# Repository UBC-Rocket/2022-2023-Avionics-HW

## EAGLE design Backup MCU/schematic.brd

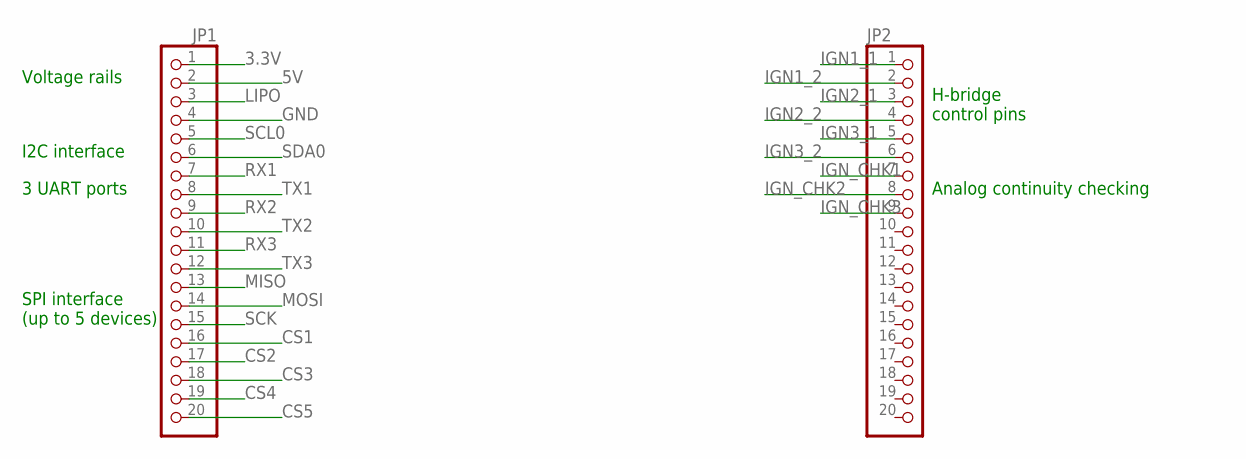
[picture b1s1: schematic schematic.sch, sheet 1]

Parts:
JP1, JP2: PINHD-1X20; 1X20

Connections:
3.3V: JP1.1; also elsewhere on the board
5V: JP1.2
CS1: JP1.16
CS2: JP1.17
CS3: JP1.18
CS4: JP1.19
CS5: JP1.20
GND: JP1.4; also elsewhere on the board
IGN1_1: JP2.1; also elsewhere on the board
IGN1_2: JP2.2; also elsewhere on the board
IGN2_1: JP2.3; also elsewhere on the board
IGN2_2: JP2.4; also elsewhere on the board
IGN3_1: JP2.5; also elsewhere on the board
IGN3_2: JP2.6; also elsewhere on the board
IGN_CHK1: JP2.7; also elsewhere on the board
IGN_CHK2: JP2.8; also elsewhere on the board
IGN_CHK3: JP2.9; also elsewhere on the board
LIPO: JP1.3; also elsewhere on the board
MISO: JP1.13
MOSI: JP1.14
RX1: JP1.7; also elsewhere on the board
RX2: JP1.9; also elsewhere on the board
RX3: JP1.11
SCK: JP1.15
SCL0: JP1.5; also elsewhere on the board
SDA0: JP1.6; also elsewhere on the board
TX1: JP1.8; also elsewhere on the board
TX2: JP1.10; also elsewhere on the board
TX3: JP1.12

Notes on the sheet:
SPI interface (up to 5 devices)
3 UART ports
I2C interface
Voltage rails
H-bridge control pins
Analog continuity checking

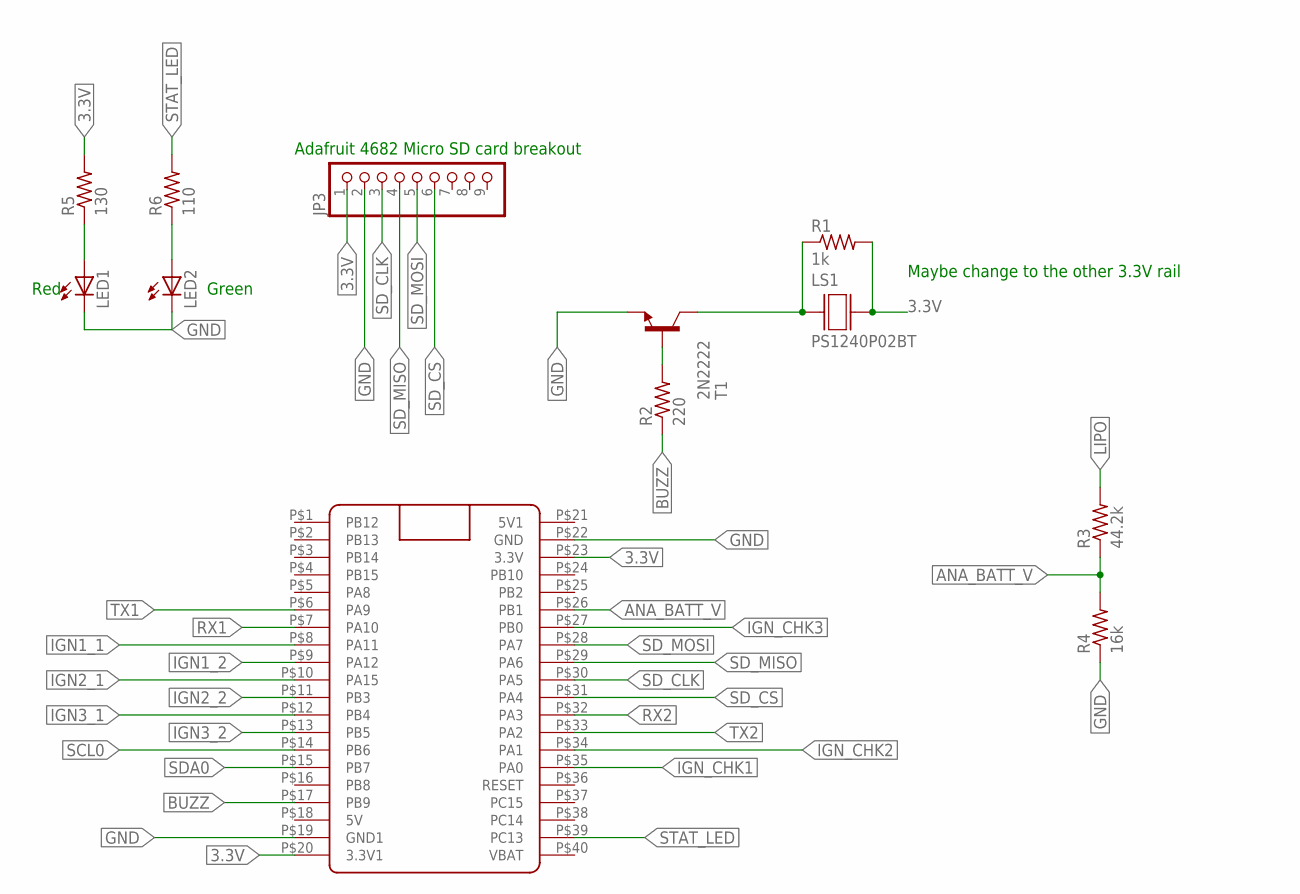
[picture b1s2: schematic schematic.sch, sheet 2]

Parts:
JP3: PINHD-1X9; 1X09-BIG
LED1, LED2: LED5MM
LS1: PS1240P02BT; XDCR_PS1240P02BT
R1: 1k; 0204/7
R2: 220; 0204/7
R3: 44.2k; 0204/7
R4: 16k; 0204/7
R5: 130; 0204/7
R6: 110; 0204/7
T1: 2N2222; TO92-EBC-OVAL
U$1: BLACK_PILL

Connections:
3.3V: JP3.1, LS1.2, R1.2, R5.2, U$1.P$20 (3.3V1), U$1.P$23 (3.3V); also elsewhere on the board
ANA_BATT_V: R3.1, R4.2, U$1.P$26 (PB1)
BUZZ: R2.1, U$1.P$17 (PB9)
GND: JP3.2, LED1.K (C), LED2.K (C), R4.1, T1.E, U$1.P$19 (GND1), U$1.P$22 (GND); also elsewhere on the board
IGN1_1: U$1.P$8 (PA11); also elsewhere on the board
IGN1_2: U$1.P$9 (PA12); also elsewhere on the board
IGN2_1: U$1.P$10 (PA15); also elsewhere on the board
IGN2_2: U$1.P$11 (PB3); also elsewhere on the board
IGN3_1: U$1.P$12 (PB4); also elsewhere on the board
IGN3_2: U$1.P$13 (PB5); also elsewhere on the board
IGN_CHK1: U$1.P$35 (PA0); also elsewhere on the board
IGN_CHK2: U$1.P$34 (PA1); also elsewhere on the board
IGN_CHK3: U$1.P$27 (PB0); also elsewhere on the board
LIPO: R3.2; also elsewhere on the board
unnamed: LS1.1, R1.1, T1.C
unnamed: LED1.A, R5.1
unnamed: R2.2, T1.B
unnamed: LED2.A, R6.1
RX1: U$1.P$7 (PA10); also elsewhere on the board
RX2: U$1.P$32 (PA3); also elsewhere on the board
SCL0: U$1.P$14 (PB6); also elsewhere on the board
SDA0: U$1.P$15 (PB7); also elsewhere on the board
SD_CLK: JP3.3, U$1.P$30 (PA5)
SD_CS: JP3.6, U$1.P$31 (PA4)
SD_MISO: JP3.4, U$1.P$29 (PA6)
SD_MOSI: JP3.5, U$1.P$28 (PA7)
STAT_LED: R6.2, U$1.P$39 (PC13)
TX1: U$1.P$6 (PA9); also elsewhere on the board
TX2: U$1.P$33 (PA2); also elsewhere on the board

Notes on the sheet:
Adafruit 4682 Micro SD card breakout
Maybe change to the other 3.3V rail
Green
Red

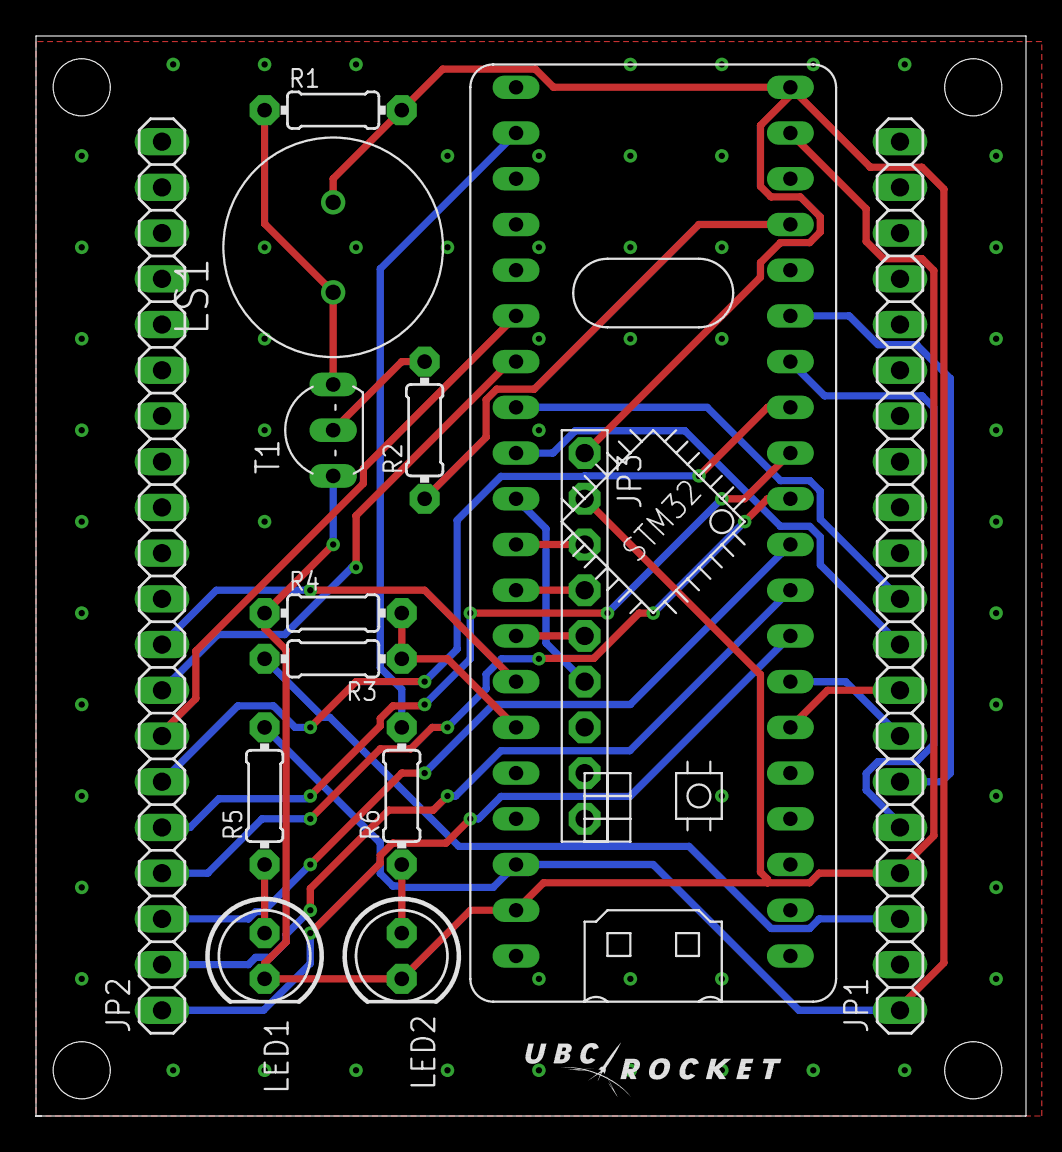
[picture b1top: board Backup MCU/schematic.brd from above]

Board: 2 copper layers, 55.0 x 60.0 mm, 14 parts (0 on the bottom side), 29 nets.

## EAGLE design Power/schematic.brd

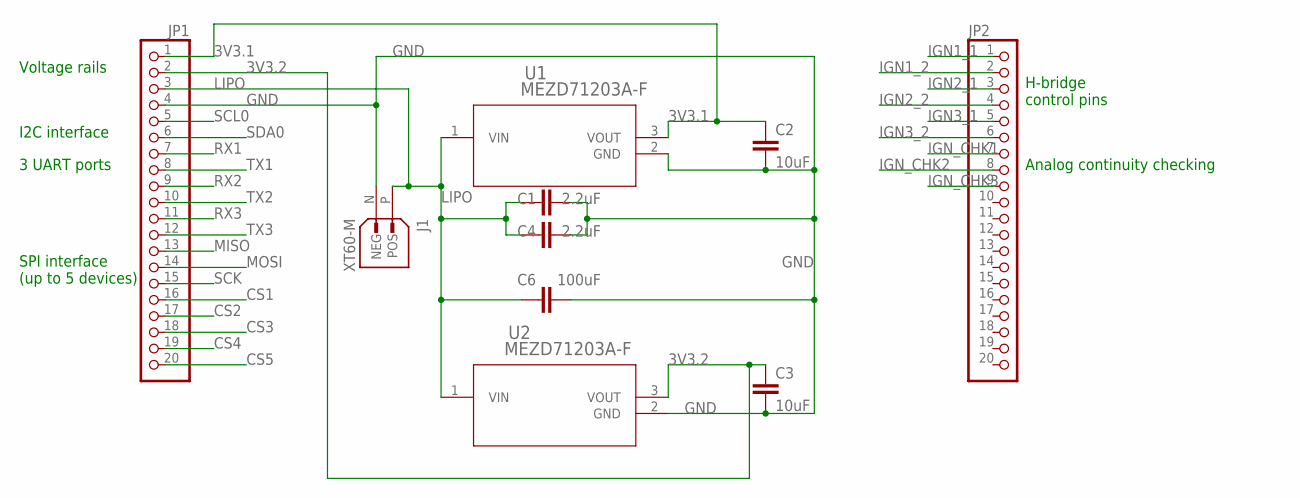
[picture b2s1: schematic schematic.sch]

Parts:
C1, C4: 2.2uF; C0805
C2, C3: 10uF; C0805
C6: 100uF; C0805
J1: XT60-M; AMASS_XT60-M
JP1, JP2: PINHD-1X20; 1X20
U1, U2: MEZD71203A-F; MEZD71203A_MNP

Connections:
3V3.1: C2.1, JP1.1, U1.3 (VOUT)
3V3.2: C3.1, JP1.2, U2.3 (VOUT)
CS1: JP1.16
CS2: JP1.17
CS3: JP1.18
CS4: JP1.19
CS5: JP1.20
GND: C1.2, C2.2, C3.2, C4.2, C6.2, J1.N (NEG), JP1.4, U1.2 (GND), U2.2 (GND)
IGN1_1: JP2.1
IGN1_2: JP2.2
IGN2_1: JP2.3
IGN2_2: JP2.4
IGN3_1: JP2.5
IGN3_2: JP2.6
IGN_CHK1: JP2.7
IGN_CHK2: JP2.8
IGN_CHK3: JP2.9
LIPO: C1.1, C4.1, C6.1, J1.P (POS), JP1.3, U1.1 (VIN), U2.1 (VIN)
MISO: JP1.13
MOSI: JP1.14
RX1: JP1.7
RX2: JP1.9
RX3: JP1.11
SCK: JP1.15
SCL0: JP1.5
SDA0: JP1.6
TX1: JP1.8
TX2: JP1.10
TX3: JP1.12

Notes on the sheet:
SPI interface (up to 5 devices)
3 UART ports
I2C interface
Voltage rails
H-bridge control pins
Analog continuity checking

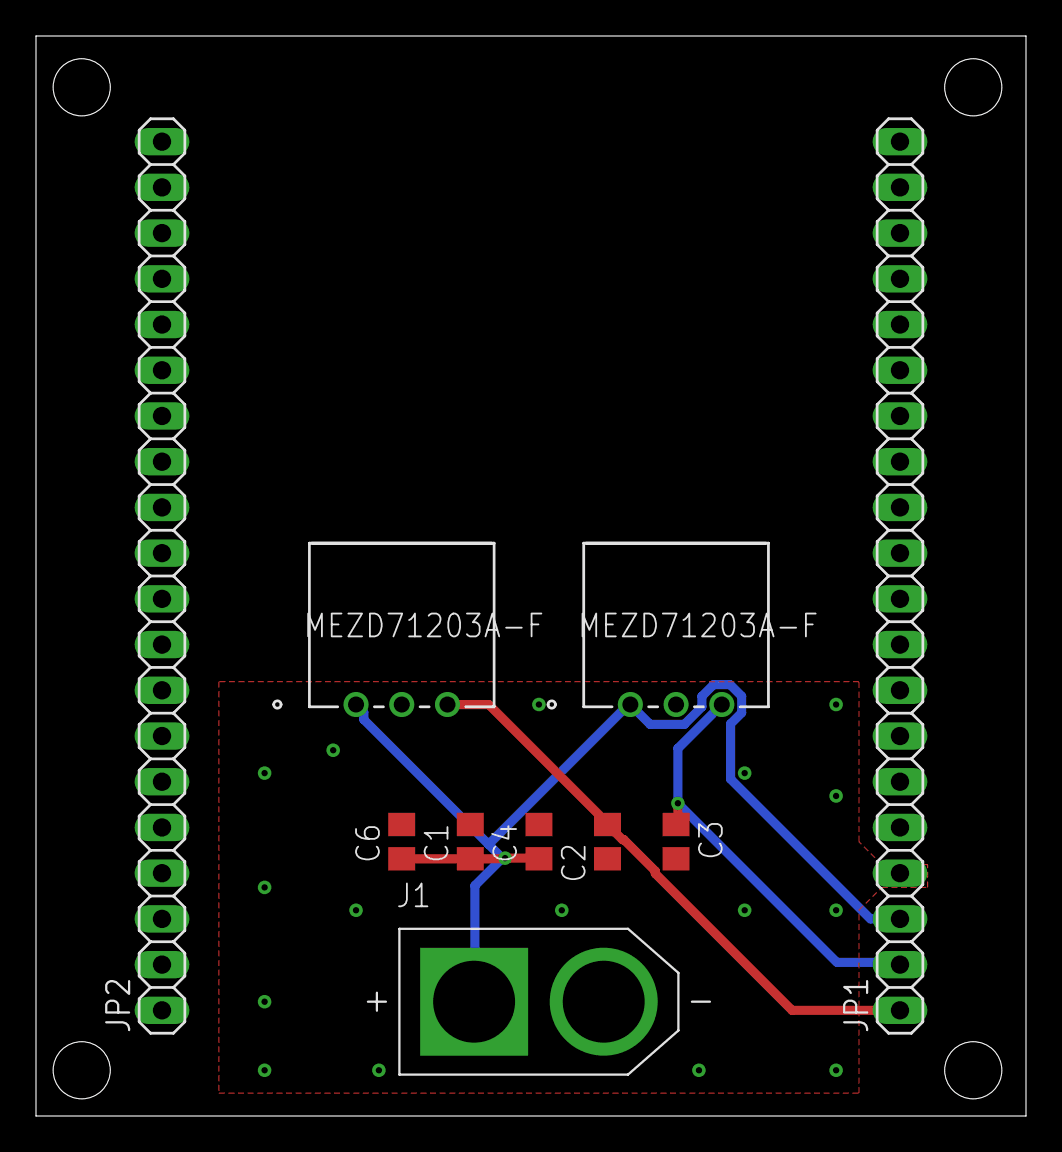
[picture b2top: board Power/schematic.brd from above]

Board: 2 copper layers, 55.0 x 60.0 mm, 10 parts (0 on the bottom side), 4 nets.

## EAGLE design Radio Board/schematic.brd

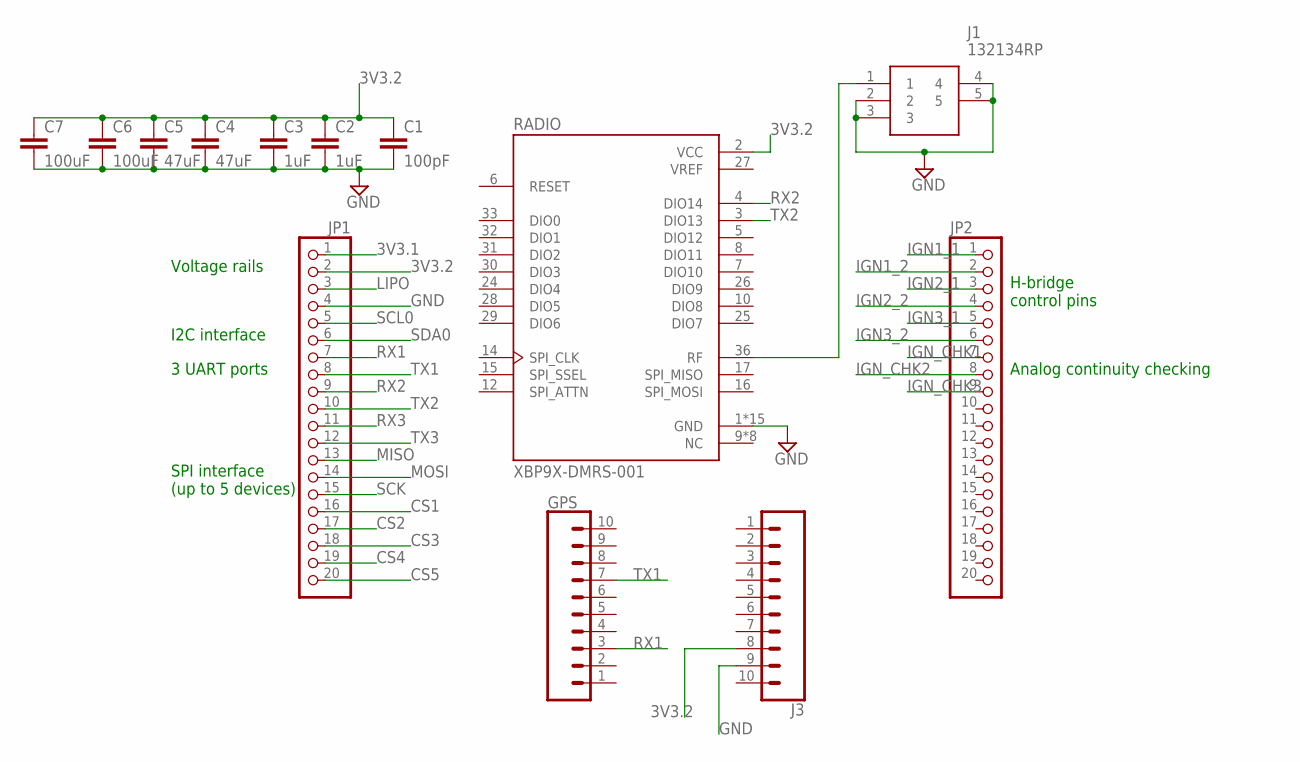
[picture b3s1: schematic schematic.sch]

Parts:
C1: 100pF; 0603
C2, C3: 1uF; 1206
C4, C5: 47uF; 1206
C6, C7: 100uF; 1206
GPS: CONN_10NO_SILK_PTH_FEMALE; 1X10_NO_SILK
J1: 132134RP
J3: CONN_10NO_SILK_PTH_FEMALE; 1X10_NO_SILK
JP1, JP2: PINHD-1X20; 1X20
RADIO: XBP9X-DMRS-001; MODULE_XBP9X-DMRS-001

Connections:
3V3.1: JP1.1
3V3.2: C1.1, C2.1, C3.1, C4.1, C5.1, C6.1, C7.1, J3.8, JP1.2, RADIO.2 (VCC)
CS1: JP1.16
CS2: JP1.17
CS3: JP1.18
CS4: JP1.19
CS5: JP1.20
GND: C1.2, C2.2, C3.2, C4.2, C5.2, C6.2, C7.2, J1.2, J1.3, J1.4, J1.5, J3.9, JP1.4, RADIO.1 (GND), RADIO.11 (GND), RADIO.13 (GND), RADIO.22 (GND), RADIO.35 (GND), RADIO.38 (GND), RADIO.V38_1 (GND), RADIO.V38_2 (GND), RADIO.V38_3 (GND), RADIO.V38_4 (GND), RADIO.V38_5 (GND), RADIO.V38_6 (GND), RADIO.V38_7 (GND), RADIO.V38_8 (GND), RADIO.V38_9 (GND)
IGN1_1: JP2.1
IGN1_2: JP2.2
IGN2_1: JP2.3
IGN2_2: JP2.4
IGN3_1: JP2.5
IGN3_2: JP2.6
IGN_CHK1: JP2.7
IGN_CHK2: JP2.8
IGN_CHK3: JP2.9
LIPO: JP1.3
MISO: JP1.13
MOSI: JP1.14
RF: J1.1, RADIO.36 (RF)
RX1: GPS.3, JP1.7
RX2: JP1.9, RADIO.4 (DIO14)
RX3: JP1.11
SCK: JP1.15
SCL0: JP1.5
SDA0: JP1.6
TX1: GPS.7, JP1.8
TX2: JP1.10, RADIO.3 (DIO13)
TX3: JP1.12
VREF: RADIO.27 (VREF)

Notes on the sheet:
SPI interface (up to 5 devices)
3 UART ports
I2C interface
Voltage rails
H-bridge control pins
Analog continuity checking

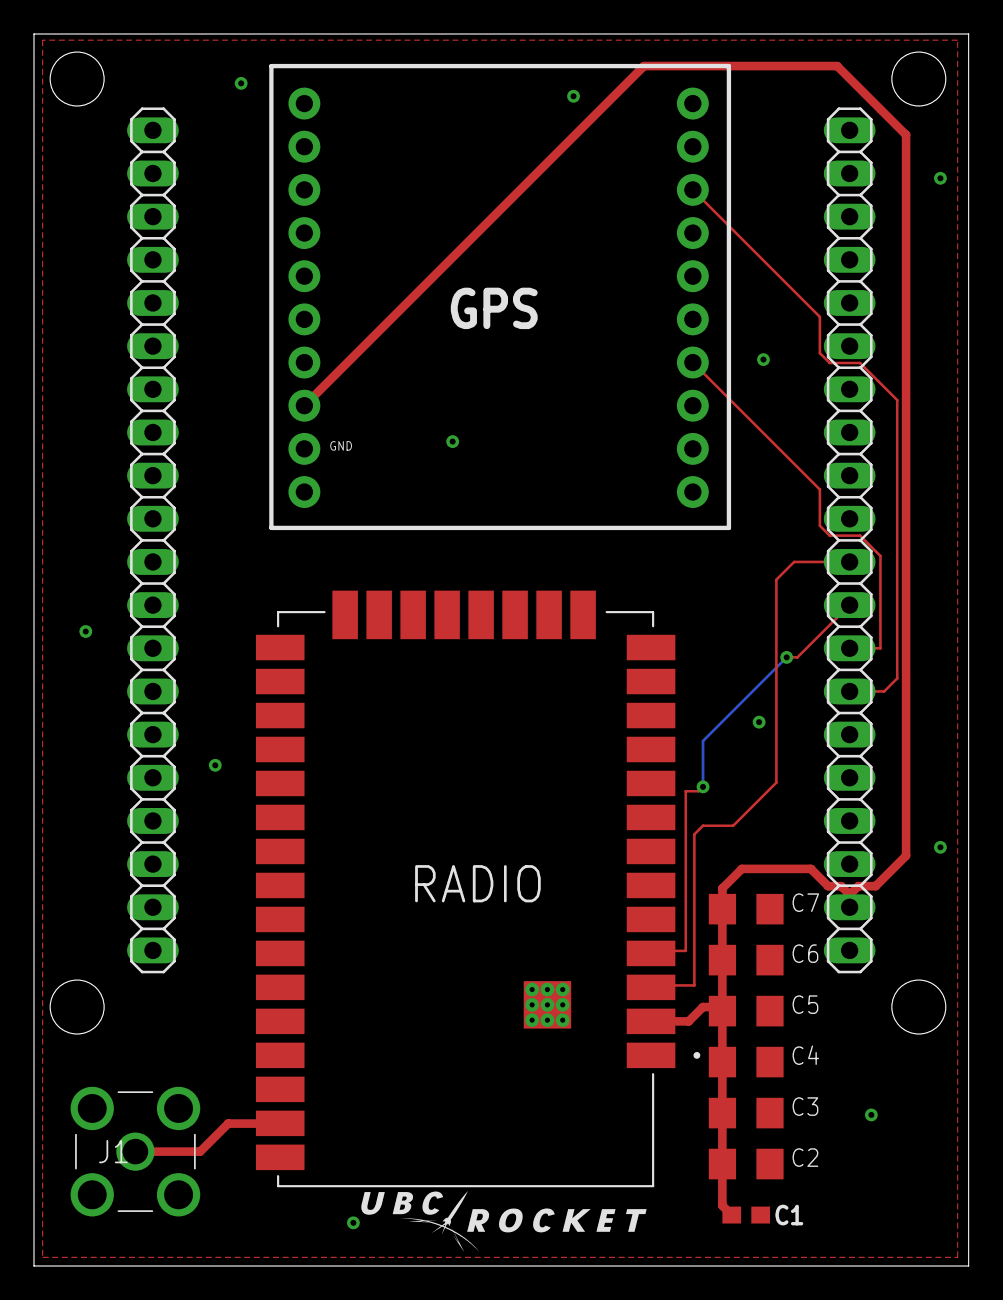
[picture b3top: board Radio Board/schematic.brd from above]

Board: 2 copper layers, 55.0 x 72.5 mm, 13 parts (0 on the bottom side), 7 nets.

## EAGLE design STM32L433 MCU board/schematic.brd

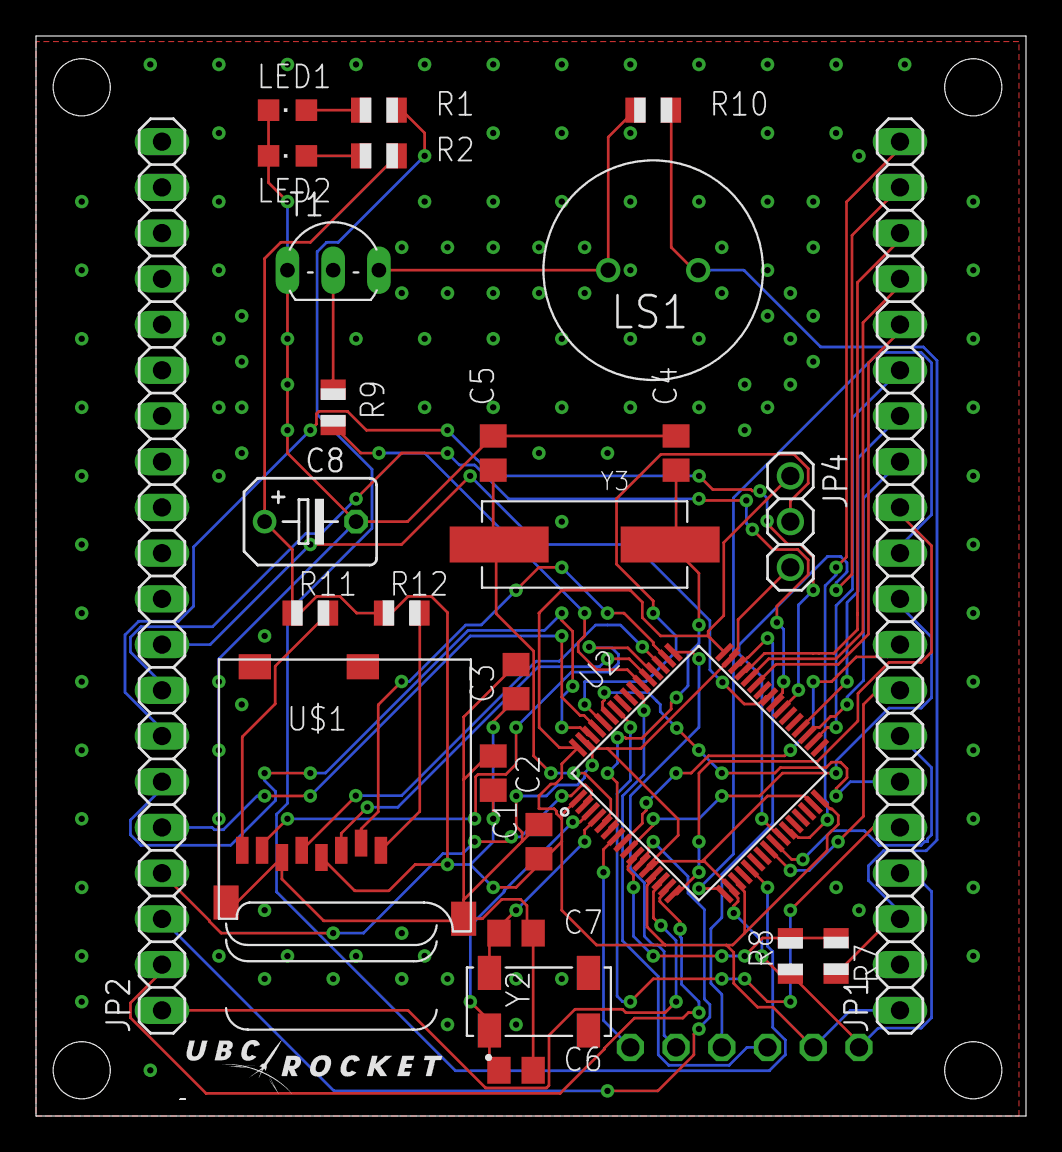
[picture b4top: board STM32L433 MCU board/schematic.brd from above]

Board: 2 copper layers, 55.0 x 60.0 mm, 28 parts (1 on the bottom side), 50 nets.

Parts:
C1: 10nF; C0805
C2: 0.1uF; C0805
C3: 1uF; C0805
C4, C5: 7pF; C0805
C6, C7: 6pF; C0805
C8: 100uF; B45181B
JP1, JP2: 1X20
JP3: 1X06
JP4: 1X03
LED1: RED; CHIPLED_0805
LED2: GREEN; CHIPLED_0805
LS1: PS1240P02BT; XDCR_PS1240P02BT
R1: 130; R0805
R2: 110; R0805
R7: 44.2k; R0805
R8: 16k; R0805
R9: 220; R0805
R10: 1k; R0805
R11, R12: 10k; R0805
T1: 2N2222; TO92-EBC-OVAL
U2: STM32L476RCT6; QFP50P120X120X160-64N
U$1: MICROSD
Y2: ABS25-32.768KHZ-6-T; XTAL_ABS25-32.768KHZ-6-T
Y3: ECS-160-S-5PX-TR; XTAL_ECS-160-S-5PX-TR

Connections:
3.3V: C1.1, C2.1, C3.1, C8.+, JP1.1, JP3.2, JP4.1, R2.2, R11.1, R12.1, U2.1, U2.13, U2.19, U2.32, U2.48, U2.64, U$1.4
ANA_BATT_V: R7.1, R8.2, U2.10
BOOT: JP4.2, U2.60
BUZZ: R9.1, U2.54
CS1: JP1.16, U2.43
CS2: JP1.17, U2.44
CS3: JP1.18, U2.45
CS4: JP1.19, U2.26
CS5: JP1.20, U2.27
GND: C1.2, C2.2, C3.2, C4.2, C5.2, C6.2, C7.2, C8.-, JP1.4, JP3.1, JP4.3, LED1.C, LED2.C, R8.1, T1.E, U2.12, U2.18, U2.31, U2.47, U2.63, U$1.6, U$1.MT1, U$1.MT2
IGN1_1: JP2.1, U2.14
IGN1_2: JP2.2, U2.15
IGN2_1: JP2.3, U2.11
IGN2_2: JP2.4, U2.2
IGN3_1: JP2.5, U2.61
IGN3_2: JP2.6, U2.62
IGN_CHK1: JP2.7, U2.39
IGN_CHK2: JP2.8, U2.40
IGN_CHK3: JP2.9, U2.41
LIPO: JP1.3, LS1.2, R7.2, R10.2
MISO: JP1.13, U2.35
MOSI: JP1.14, U2.36
unnamed: C5.1, U2.5, Y3.1
unnamed: R9.2, T1.B
unnamed: LS1.1, R10.1, T1.C
unnamed: R11.2, U$1.8
unnamed: C4.1, U2.6, Y3.2
unnamed: R12.2, U$1.1
unnamed: LED1.A, R1.1
unnamed: LED2.A, R2.1
unnamed: C7.1, U2.4, Y2.4
unnamed: C6.1, U2.3, Y2.1
NRST: JP3.6, U2.7
RX1: JP1.7, U2.25
RX2: JP1.9, U2.8
RX3: JP1.11, U2.17
SCK: JP1.15, U2.34
SCL0: JP1.5, U2.58
SDA0: JP1.6, U2.59
SD_CS: U2.50, U$1.2
SPI1_MISO: U2.52, U$1.7
SPI1_MOSI: U2.53, U$1.3
SPI1_SCK: U2.51, U$1.5
STAT_LED: R1.2, U2.21
SWCLK: JP3.5, U2.49
SWDIO: JP3.4, U2.46
SWO: JP3.3, U2.55
TX1: JP1.8, U2.24
TX2: JP1.10, U2.9
TX3: JP1.12, U2.16

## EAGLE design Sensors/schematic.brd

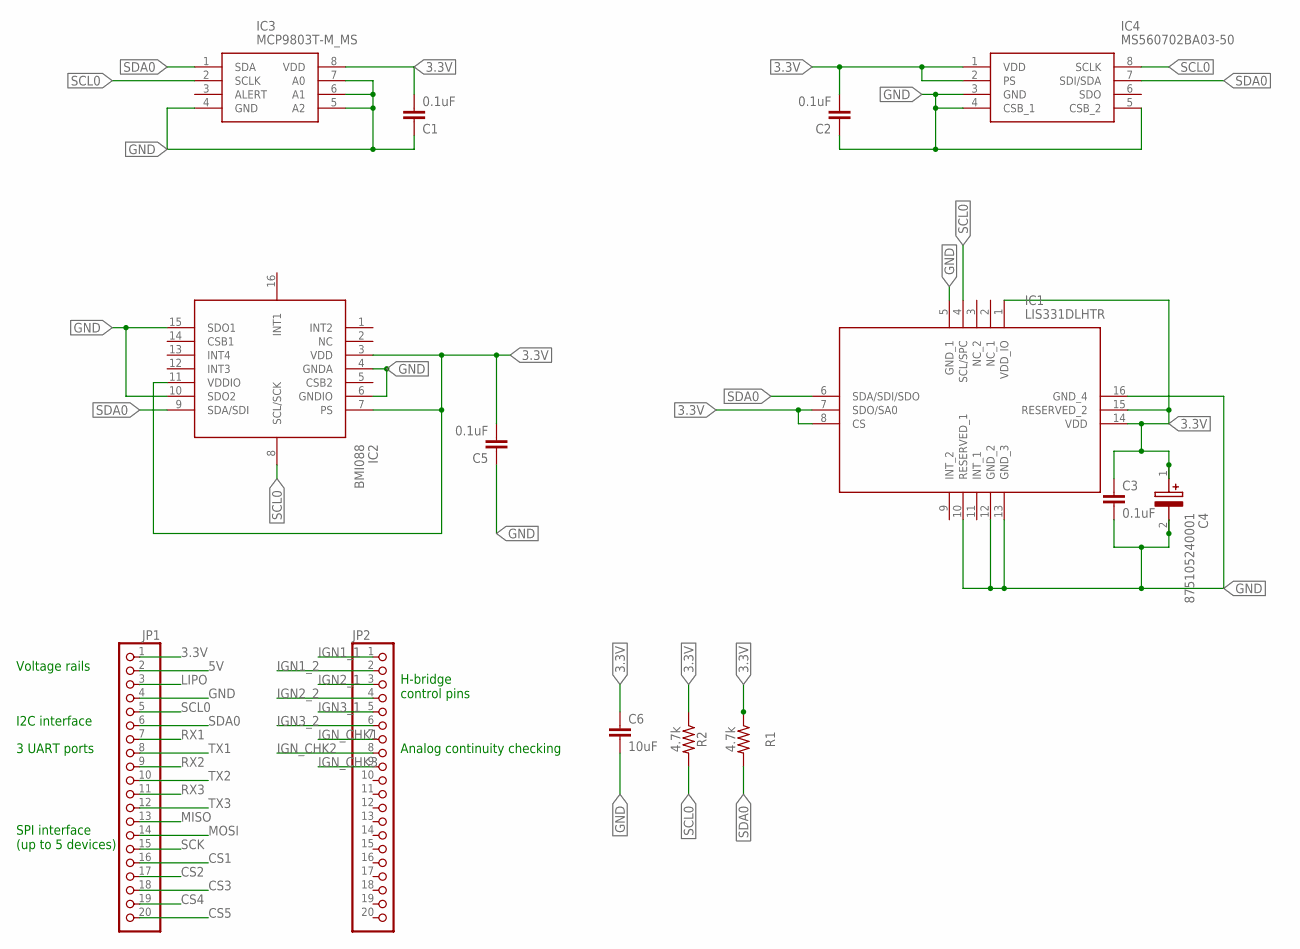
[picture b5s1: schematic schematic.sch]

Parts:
C1, C2, C3, C5: 0.1uF; 0805
C4: 875105240001; CAPAE430X550N
C6: 10uF; 0805
IC1: LIS331DLHTR
IC2: BMI088
IC3: MCP9803T-M_MS; SOP65P490X110-8N
IC4: MS560702BA03-50; MS5607-02BA03
JP1, JP2: PINHD-1X20; 1X20
R1, R2: 4.7k; 0805

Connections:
3.3V: C1.2, C2.2, C3.2, C4.1 (+), C5.2, C6.1, IC1.1 (VDD_IO), IC1.7 (SDO/SA0), IC1.8 (CS), IC1.14 (VDD), IC1.15 (RESERVED_2), IC2.3 (VDD), IC2.7 (PS), IC2.11 (VDDIO), IC3.8 (VDD), IC4.1 (VDD), IC4.2 (PS), JP1.1, R1.1, R2.1
5V: JP1.2
CS1: JP1.16
CS2: JP1.17
CS3: JP1.18
CS4: JP1.19
CS5: JP1.20
GND: C1.1, C2.1, C3.1, C4.2 (-), C5.1, C6.2, IC1.5 (GND_1), IC1.10 (RESERVED_1), IC1.12 (GND_2), IC1.13 (GND_3), IC1.16 (GND_4), IC2.4 (GNDA), IC2.6 (GNDIO), IC2.10 (SDO2), IC2.15 (SDO1), IC3.4 (GND), IC3.5 (A2), IC3.6 (A1), IC3.7 (A0), IC4.3 (GND), IC4.4 (CSB_1), IC4.5 (CSB_2), JP1.4
IGN1_1: JP2.1
IGN1_2: JP2.2
IGN2_1: JP2.3
IGN2_2: JP2.4
IGN3_1: JP2.5
IGN3_2: JP2.6
IGN_CHK1: JP2.7
IGN_CHK2: JP2.8
IGN_CHK3: JP2.9
LIPO: JP1.3
MISO: JP1.13
MOSI: JP1.14
RX1: JP1.7
RX2: JP1.9
RX3: JP1.11
SCK: JP1.15
SCL0: IC1.4 (SCL/SPC), IC2.8 (SCL/SCK), IC3.2 (SCLK), IC4.8 (SCLK), JP1.5, R2.2
SDA0: IC1.6 (SDA/SDI/SDO), IC2.9 (SDA/SDI), IC3.1 (SDA), IC4.7 (SDI/SDA), JP1.6, R1.2
TX1: JP1.8
TX2: JP1.10
TX3: JP1.12

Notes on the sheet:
SPI interface (up to 5 devices)
3 UART ports
I2C interface
Voltage rails
H-bridge control pins
Analog continuity checking

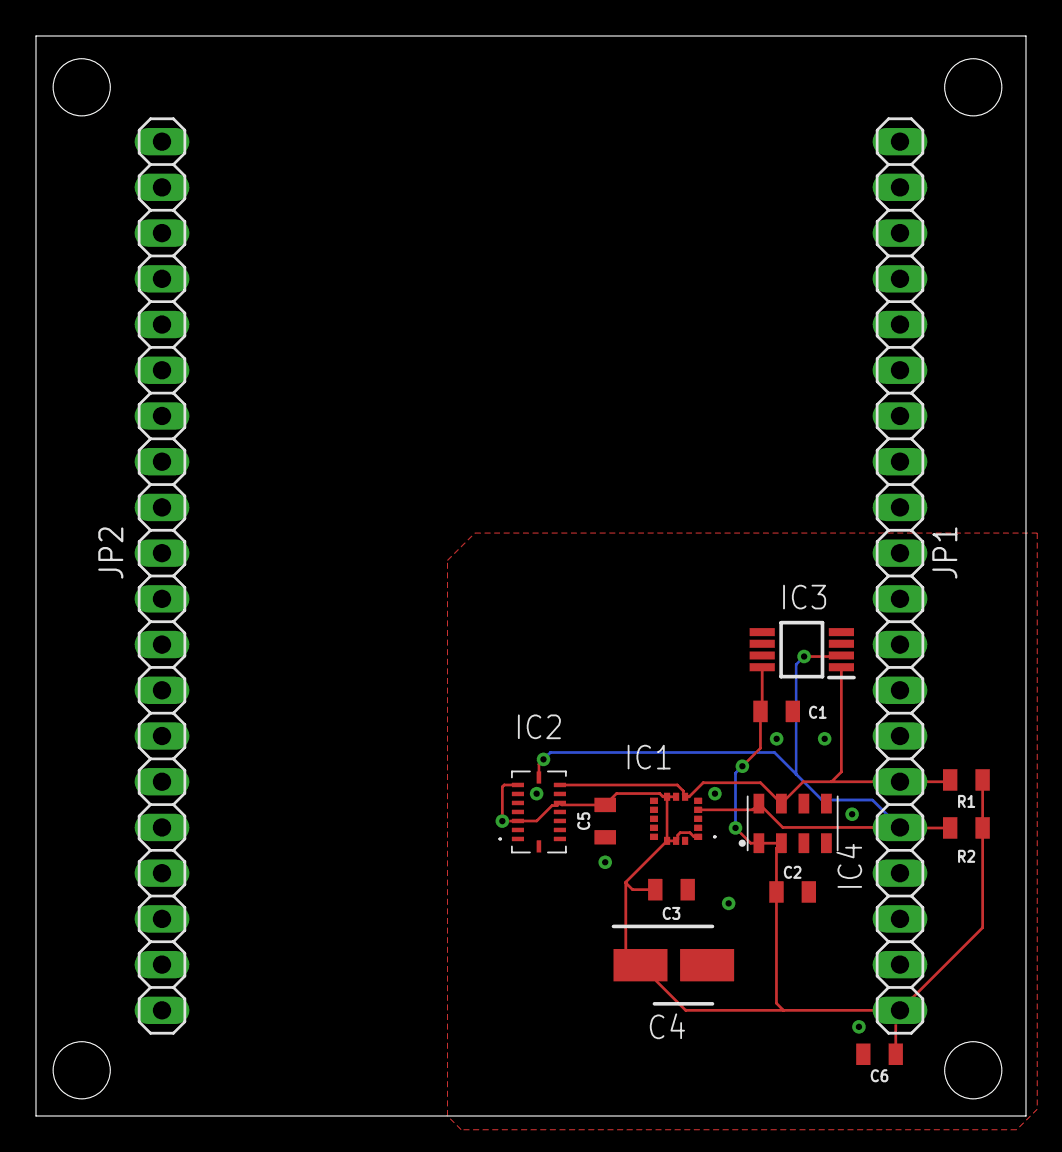
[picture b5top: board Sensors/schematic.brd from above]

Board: 2 copper layers, 55.0 x 60.0 mm, 14 parts (0 on the bottom side), 4 nets.

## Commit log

2022-10-23 Copy Template for Radio Avionics
2022-10-23 Added Radio part
2022-11-01 Added correct radio board
2022-11-06 Added GPS module and complementary components
2022-11-12 created ignition folder with altium files
2022-11-12 Placing Components finished
2022-11-12 Finished wiring
2022-11-12 Finished Routing
2022-11-12 gitignore
2022-11-12 fixed git ignore
2022-11-17 created optocoupler schematic and footprint
2022-11-17 Added optoisolators to schematic, wire another igniter
2022-11-17 Added optoisolators to schematic, wired another igniter
2022-11-20 updated PCB layout, still need to add continuity checking
2022-11-20 changed opto resistors, added new opto for last continuity check
2022-11-21 Updated radio & GPS
2022-11-21 Finished MCU board routing
2022-11-27 Modifying after EDR
2022-11-27 added a 100uF cap
2022-11-28 Added voltage divider, changed top igniter reference, added pulldown and pullup for ingition fets, changed resitor values.
2022-11-28 Added voltage dividers, changed resistor values, added pullup and pulldown for igniter fets, changed layout
2022-11-28 Added voltage divider, changed resistor values, added pulldown and pullup for igniter fets.
2022-11-28 did some routing
2022-12-01 removed unnecessary files
2022-12-01 updated radio
2022-12-03 Radio Board - Routed traces, missing ground plane
2022-12-03 Planes included, added backups to gitignore
2022-12-04 Flipped GPS Module
2022-12-04 moved radio silkscreen
2022-12-04 Added Ethan's stuff
2022-12-05 got rid of half-bridge
2022-12-24 did some autorouting, added ground plane on top layer
2022-12-25 Finished routing, created output files
2022-12-25 finished layout
2022-12-25 finished layout, added output fi;es
2023-01-03 upload final power board
2023-01-06 Added NC Drill files
2023-01-15 Uploaded manufactured PCB design
    Doesn't include battery voltage wire :(
2023-01-22 Made some necessary changes for batch 2 :(
    That moment when you don't ground the output of oscillators and you don't connect a whole signal lol. At least we get a chance to refine the board
2023-02-05 switched from using rxa to rxb
2023-02-24 Replaced oscillator components and re-ran autorouter
    Still need to route some other wires and check if pinout is good
2023-02-25 Added gitignore
2023-03-04 Finished routing and ground plane stitching
2023-03-04 Added logo
2023-03-06 fixed wiring on radio board
2023-03-19 March 19th pre-edit update
2023-03-19 March 19th update
2023-03-19 removed opto on continuity checking, and made lipo holes larger
2023-04-02 New board using a black pill STM32 dev board
2023-04-22 Additional changes for backup MCU
2023-06-16 Started a new MCU PCB design using Altium by actually reading the app note
2024-03-03 New MCU board before board order

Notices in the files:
parts and their libraries:
COPYRIGHT: Copyright (C) 2022 Ultra Librarian. All rights reserved.
SparkFun-Connectors: Licensing: Creative Commons ShareAlike 4.0 International - https://creativecommons.org/licenses/by-sa/4.0
